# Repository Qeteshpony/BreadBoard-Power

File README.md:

# BreadBoard-Power

[Hardware Documentation](https://qeteshpony.github.io/BreadBoard-Power)

A little tool to make prototyping on a solderless breadboard a little easier. Most cheap breadboard power supplies need a lot of space and dont offer modern connections. This one has a USB-C connector as input, is as slim as possible so it can be placed basically anywhere on the breadboard and it has a 1A 3.3V voltage regulator included that allows to put 3.3V on a rail. 

The project includes all production files to get the SMT parts assembled by JLCPCB (not a sponsor) but I used hand-solder-footprints for the smaller parts so it should be quite easy to solder manually, too.

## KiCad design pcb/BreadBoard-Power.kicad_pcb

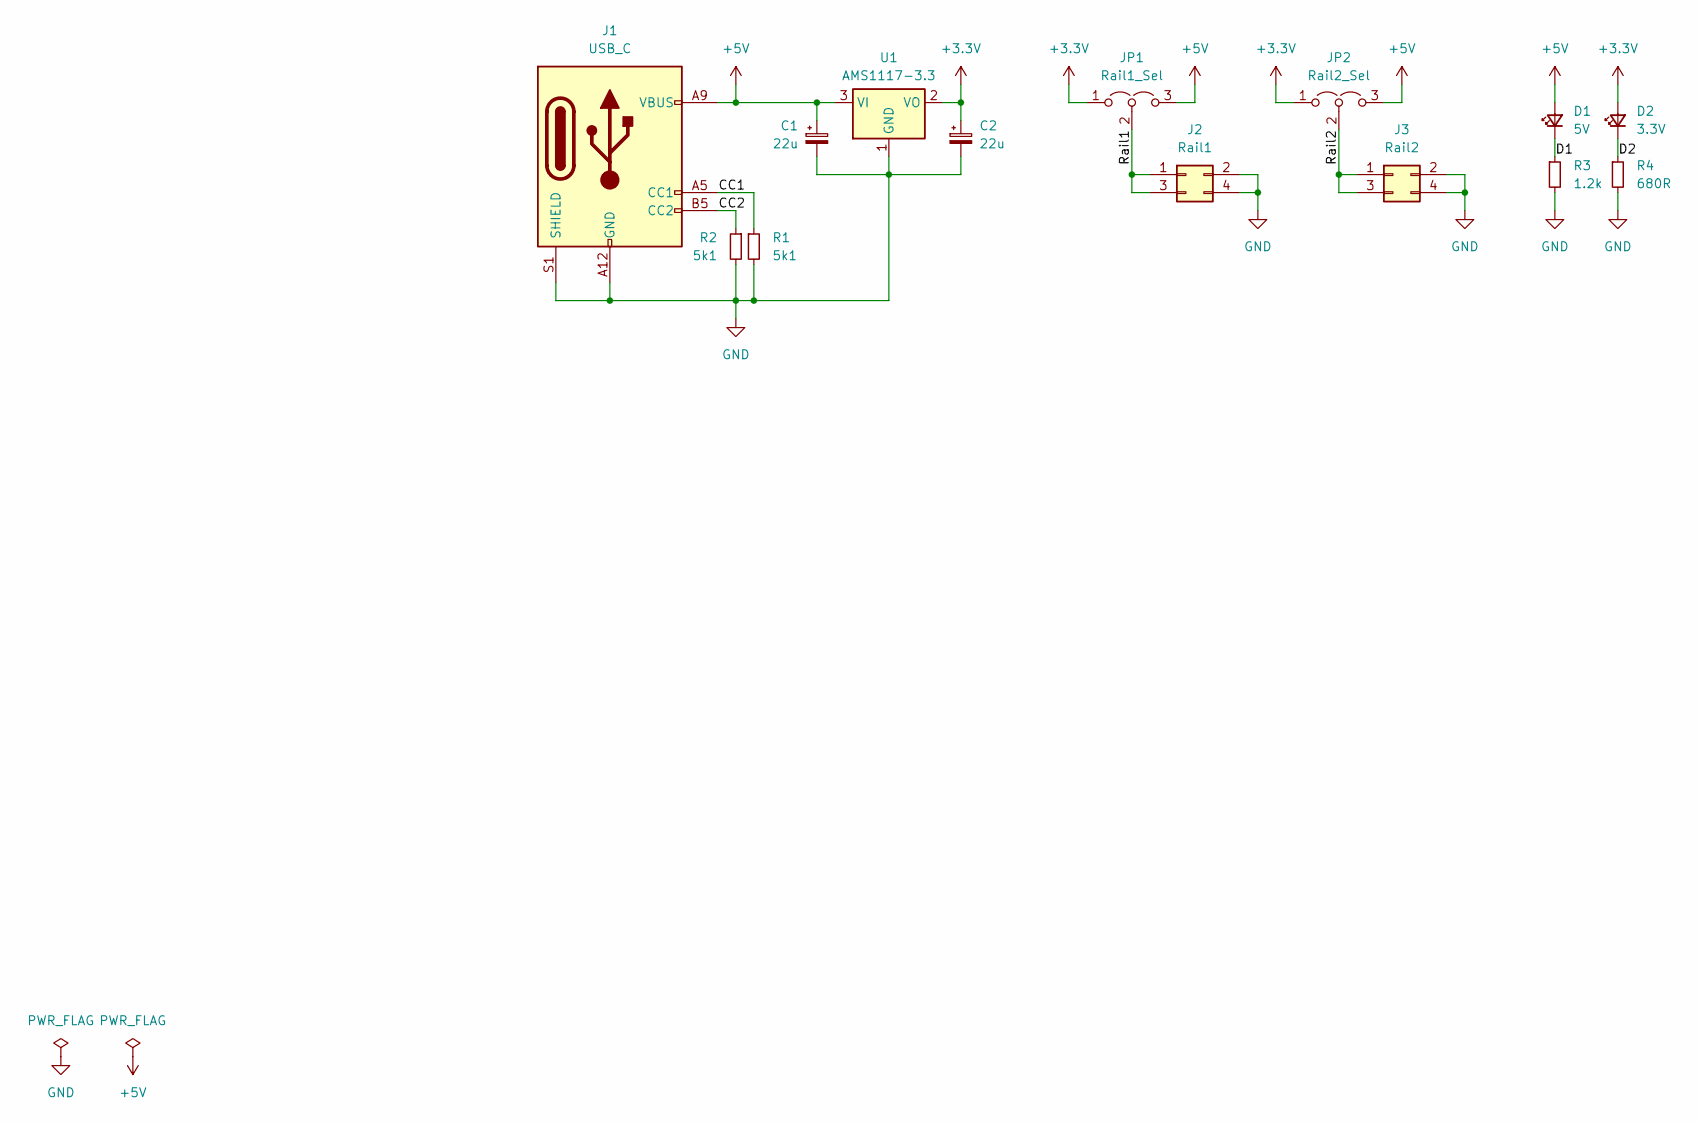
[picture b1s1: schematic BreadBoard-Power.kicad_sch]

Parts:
C1, C2: 22u; CP_EIA-3216-18_Kemet-A_Pad1.58x1.35mm_HandSolder; LCSC C7171
D1: 5V; LED_0603_1608Metric_Pad1.05x0.95mm_HandSolder; LCSC C2286
D2: 3.3V; LED_0603_1608Metric_Pad1.05x0.95mm_HandSolder; LCSC C2286
J1: USB_C; USB_C_Receptacle_GCT_USB4125-xx-x_6P_TopMnt_Horizontal; LCSC C2763104
J2: Rail1; PinHeader_2x02_P2.54mm_Vertical
J3: Rail2; PinHeader_2x02_P2.54mm_Vertical
JP1: Rail1_Sel; PinHeader_1x03_P2.54mm_Vertical
JP2: Rail2_Sel; PinHeader_1x03_P2.54mm_Vertical
R1, R2: 5k1; R_0603_1608Metric_Pad0.98x0.95mm_HandSolder; LCSC C23186
R3: 1.2k; R_0603_1608Metric_Pad0.98x0.95mm_HandSolder; LCSC C22765
R4: 680R; R_0603_1608Metric_Pad0.98x0.95mm_HandSolder; LCSC C23228
U1: AMS1117-3.3; SOT-223-3_TabPin2; LCSC C6186

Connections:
+3.3V: C2.1, D2.2 (A), JP1.1 (A), JP2.1 (A), U1.2 (VO)
+5V: C1.1, D1.2 (A), J1.A9 (VBUS), J1.B9 (VBUS), JP1.3 (B), JP2.3 (B), U1.3 (VI)
/CC1: J1.A5 (CC1), R1.1
/CC2: J1.B5 (CC2), R2.1
/D1: D1.1 (K), R3.1
/D2: D2.1 (K), R4.1
/Rail1: J2.1, J2.3, JP1.2 (C)
/Rail2: J3.1, J3.3, JP2.2 (C)
GND: C1.2, C2.2, J1.A12 (GND), J1.B12 (GND), J1.S1 (SHIELD), J2.2, J2.4, J3.2, J3.4, R1.2, R2.2, R3.2, R4.2, U1.1 (GND)

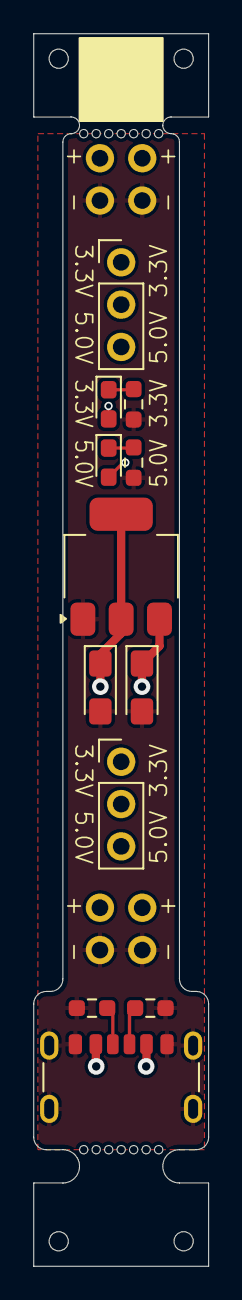
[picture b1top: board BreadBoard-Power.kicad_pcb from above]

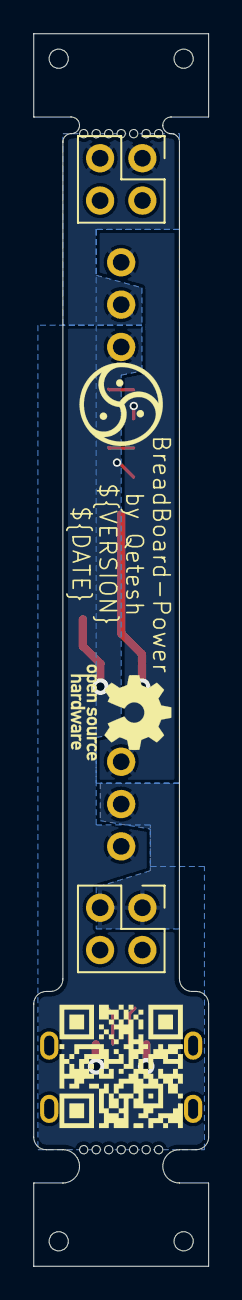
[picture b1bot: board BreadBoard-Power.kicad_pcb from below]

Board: 2 copper layers, 10.5 x 74.0 mm, 16 parts (2 on the bottom side), 9 nets.

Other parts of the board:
mouse-bite-2mm-slot: VAL**; mouse-bite-2x5mm-slot-onesided-v2
mouse-bite-2mm-slot#2: VAL**; mouse-bite-2x5mm-slot-onesided-no-edge

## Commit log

2024-07-31 feat: initial commit
2024-08-21 docs: schematic cleanup
2024-08-21 chore(main): release 1.0.0
2024-08-21 fix: add missing logos
2024-08-21 chore(main): release 1.0.1
2024-08-21 ci: remove dependency for parallel running
2024-08-22 ci: change 3d render angle
2024-08-22 feat: add production rails
2024-08-22 chore(main): release 1.1.0
